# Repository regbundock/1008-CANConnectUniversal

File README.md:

1009-CANConnectUniversal

This board is multi-functional. It connects the CBUS module or modules to
the ribbon cable, it accepts power from a 12V suupply, allows the +12V
power line to be broken to provide an isolated power zone ang provides an
interface for a CANCAB.

It provides all that is necessary to run a small CBUS system for testing.
A CANUSB4 is also needed to allow the FCU or JMRI to be used.

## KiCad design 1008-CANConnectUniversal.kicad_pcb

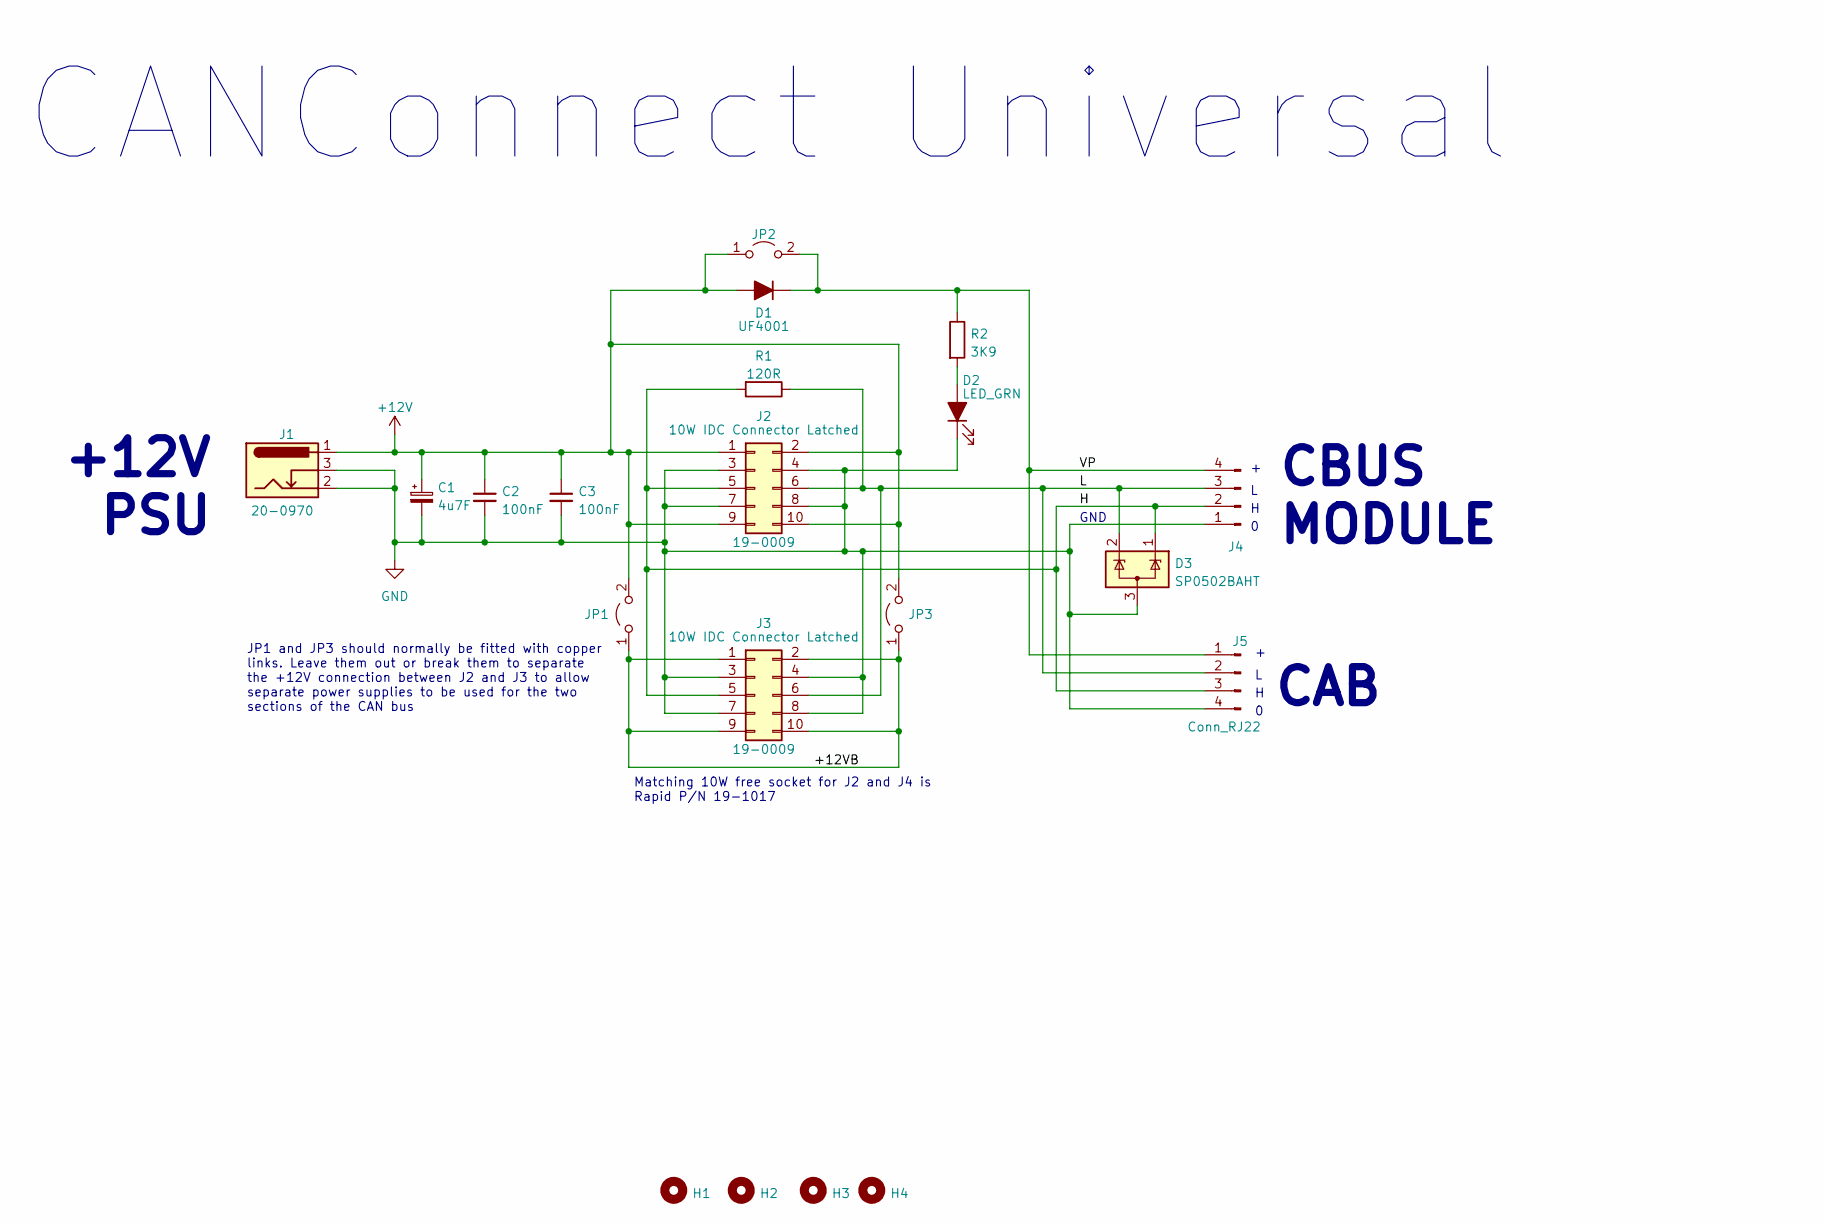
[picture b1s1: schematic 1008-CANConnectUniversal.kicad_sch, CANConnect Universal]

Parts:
C1: 4u7F; CP_Radial_Tantal_D5.0mm_P2.50mm
C2, C3: 100nF; C_Disc_D5.0mm_W2.5mm_P5.00mm
D1: UF4001; D_DO-41_SOD81_P10.16mm_Horizontal
D2: LED_GRN; LED_D3.0mm
D3: SP0502BAHT; SOT-23
H1, H2, H3, H4: MountingHole; MountingHole_3.2mm_M3
J1: 2.1mm PCB Power Socket; BarrelJack_Horizontal; Part no. 20-0970
J2, J3: 10W IDC Connector Latched; IDC-Header_2x05_P2.54mm_Latch_Vertical; Part No. 19-0009
J4: Conn_01x04_Male; Camdenboss_3pt5mm_pitch_PCB_horizontal_4Way
J5: Conn_RJ22; RJ22
JP1, JP2, JP3: Jumper_2_Open; PinHeader_1x02_P2.54mm_Vertical
R1: 120R; R_Axial_P10.16mm_Horizontal
R2: 3K9; R_Axial_P10.16mm_Horizontal

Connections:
+12V: C1.1, C2.1, C3.1, D1.2 (A), J1.1, J2.1, J2.2, J2.9, J2.10, JP1.2 (B), JP2.1 (A), JP3.2 (B)
/+12VB: J3.1, J3.2, J3.9, J3.10, JP1.1 (A), JP3.1 (A)
/H: D3.1 (K), J2.5, J3.5, J4.2, J5.3, R1.2
/L: D3.2 (K), J2.6, J3.6, J4.3, J5.2, R1.1
/VP: D1.1 (K), J4.4, J5.1, JP2.2 (B), R2.1
GND: C1.2, C2.2, C3.2, D2.1 (K), D3.3 (A), J1.2, J1.3, J2.3, J2.4, J2.7, J2.8, J3.3, J3.4, J3.7, J3.8, J4.1, J5.4
unnamed: D2.2 (A), R2.2

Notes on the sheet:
CANConnect Universal
JP1 and JP3 should normally be fitted with copper links. Leave them out or break them to separate the +12V connection between J2 and J3 to allow separate power supplies to be used for the two sections of the CAN bus
CAB
+12V PSU
GND
CBUS MODULE
Matching 10W free socket for J2 and J4 is Rapid P/N 19-1017

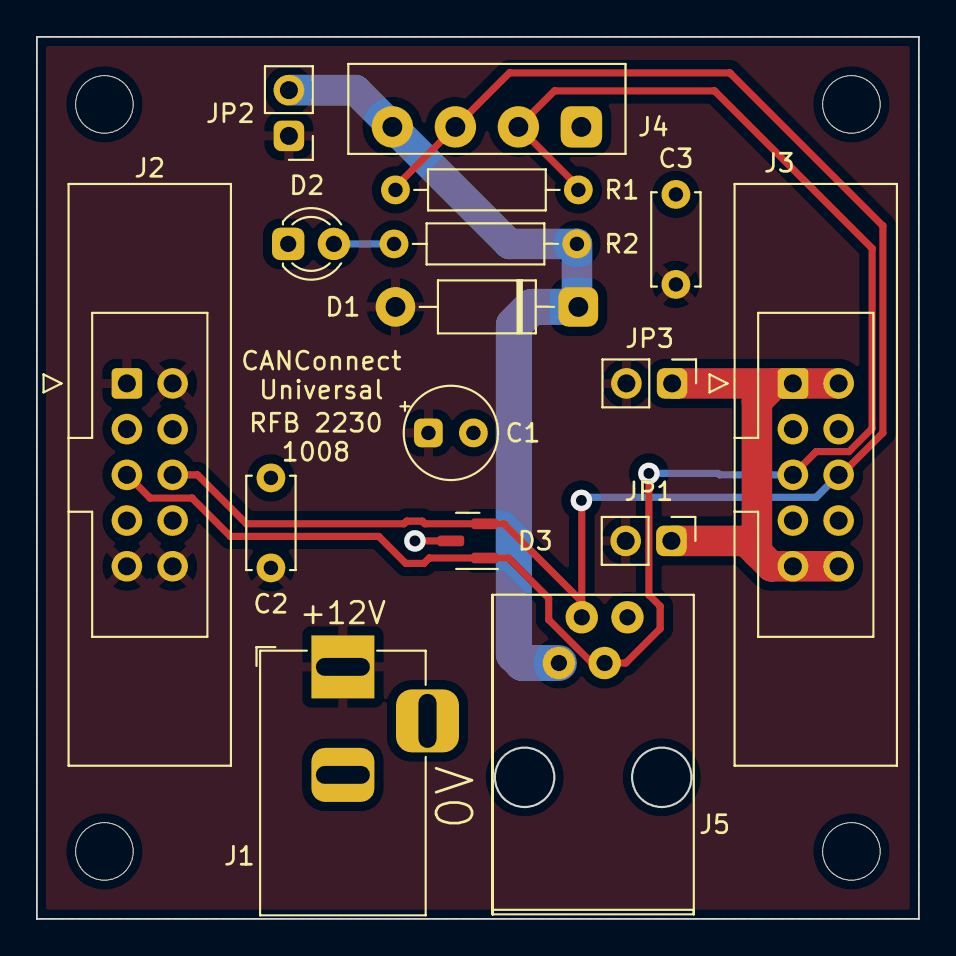
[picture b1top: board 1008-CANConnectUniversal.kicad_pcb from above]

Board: 2 copper layers, 49.0 x 49.0 mm, 20 parts (0 on the bottom side), 7 nets.
